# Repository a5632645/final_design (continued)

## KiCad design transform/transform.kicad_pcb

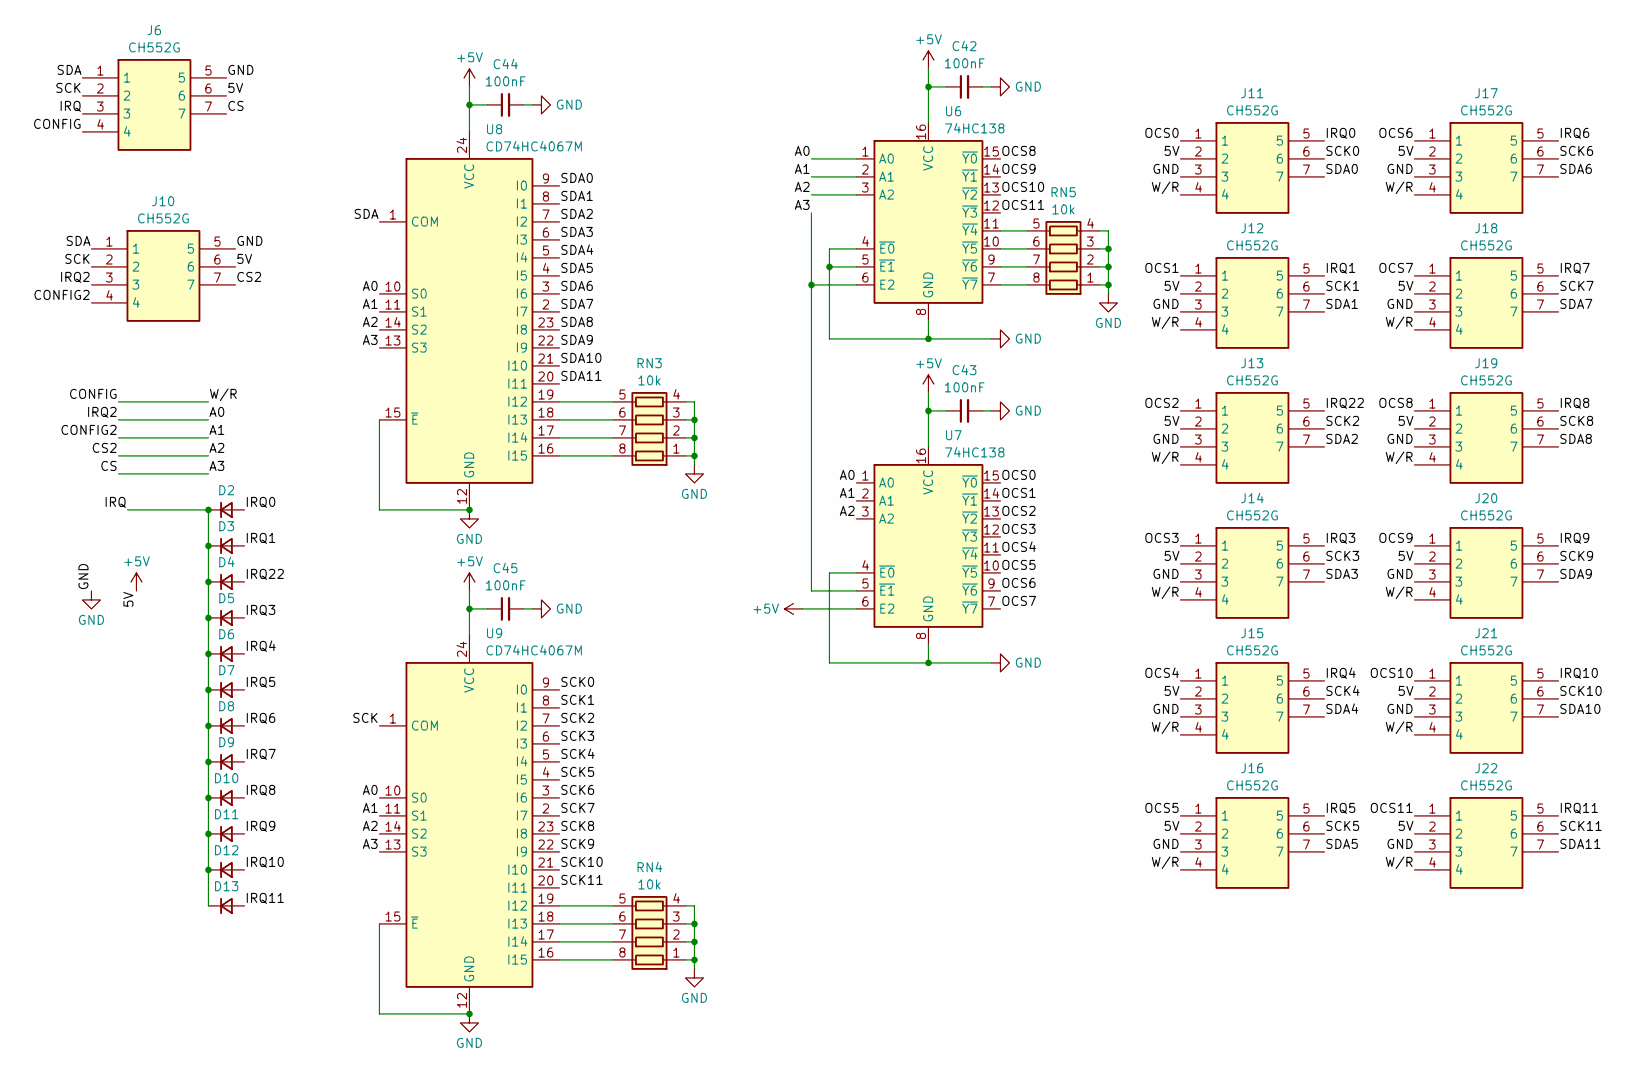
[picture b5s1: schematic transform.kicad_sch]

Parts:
C42, C43, C44, C45: 100nF; C_0603_1608Metric
D2, D3, D4, D5, D6, D7, D8, D9, D10, D11, D12, D13: D_Small; D_1206_3216Metric
J6, J10, J11, J12, J13, J14, J15, J16, J17, J18, J19, J20, J21, J22: CH552G; SM07B-SRSS-TB; Manufacturer_Part_Number SM07B-SRSS-TB (LF)(SN)
RN3, RN4, RN5: 10k; R_Array_Convex_4x0603
U6, U7: 74HC138; SOIC-16_3.9x9.9mm_P1.27mm
U8, U9: CD74HC4067M; SOIC-24W_7.5x15.4mm_P1.27mm

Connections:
+5V: C42.1, C43.1, C44.1, C45.1, J6.6, J10.6, J11.2, J12.2, J13.2, J14.2, J15.2, J16.2, J17.2, J18.2, J19.2, J20.2, J21.2, J22.2, U6.16 (VCC), U7.6 (E2), U7.16 (VCC), U8.24 (VCC), U9.24 (VCC)
/A0: J10.3, U6.1 (A0), U7.1 (A0), U8.10 (S0), U9.10 (S0)
/A1: J10.4, U6.2 (A1), U7.2 (A1), U8.11 (S1), U9.11 (S1)
/A2: J10.7, U6.3 (A2), U7.3 (A2), U8.14 (S2), U9.14 (S2)
/A3: J6.7, U6.6 (E2), U7.5 (~E1), U8.13 (S3), U9.13 (S3)
/CONFIG: J6.4, J11.4, J12.4, J13.4, J14.4, J15.4, J16.4, J17.4, J18.4, J19.4, J20.4, J21.4, J22.4
/IRQ: D2.1 (K), D3.1 (K), D4.1 (K), D5.1 (K), D6.1 (K), D7.1 (K), D8.1 (K), D9.1 (K), D10.1 (K), D11.1 (K), D12.1 (K), D13.1 (K), J6.3
/IRQ0: D2.2 (A), J11.5
/IRQ1: D3.2 (A), J12.5
/IRQ3: D5.2 (A), J14.5
/IRQ4: D6.2 (A), J15.5
/IRQ5: D7.2 (A), J16.5
/IRQ6: D8.2 (A), J17.5
/IRQ7: D9.2 (A), J18.5
/IRQ8: D10.2 (A), J19.5
/IRQ9: D11.2 (A), J20.5
/IRQ10: D12.2 (A), J21.5
/IRQ11: D13.2 (A), J22.5
/IRQ22: D4.2 (A), J13.5
/OCS0: J11.1, U7.15 (~Y0)
/OCS1: J12.1, U7.14 (~Y1)
/OCS2: J13.1, U7.13 (~Y2)
/OCS3: J14.1, U7.12 (~Y3)
/OCS4: J15.1, U7.11 (~Y4)
/OCS5: J16.1, U7.10 (~Y5)
/OCS6: J17.1, U7.9 (~Y6)
/OCS7: J18.1, U7.7 (~Y7)
/OCS8: J19.1, U6.15 (~Y0)
/OCS9: J20.1, U6.14 (~Y1)
/OCS10: J21.1, U6.13 (~Y2)
/OCS11: J22.1, U6.12 (~Y3)
/SCK: J6.2, J10.2, U9.1 (COM)
/SCK0: J11.6, U9.9 (I0)
/SCK1: J12.6, U9.8 (I1)
/SCK2: J13.6, U9.7 (I2)
/SCK3: J14.6, U9.6 (I3)
/SCK4: J15.6, U9.5 (I4)
/SCK5: J16.6, U9.4 (I5)
/SCK6: J17.6, U9.3 (I6)
/SCK7: J18.6, U9.2 (I7)
/SCK8: J19.6, U9.23 (I8)
/SCK9: J20.6, U9.22 (I9)
/SCK10: J21.6, U9.21 (I10)
/SCK11: J22.6, U9.20 (I11)
/SDA: J6.1, J10.1, U8.1 (COM)
/SDA0: J11.7, U8.9 (I0)
/SDA1: J12.7, U8.8 (I1)
/SDA2: J13.7, U8.7 (I2)
/SDA3: J14.7, U8.6 (I3)
/SDA4: J15.7, U8.5 (I4)
/SDA5: J16.7, U8.4 (I5)
/SDA6: J17.7, U8.3 (I6)
/SDA7: J18.7, U8.2 (I7)
/SDA8: J19.7, U8.23 (I8)
/SDA9: J20.7, U8.22 (I9)
/SDA10: J21.7, U8.21 (I10)
/SDA11: J22.7, U8.20 (I11)
GND: C42.2, C43.2, C44.2, C45.2, J6.5, J10.5, J11.3, J12.3, J13.3, J14.3, J15.3, J16.3, J17.3, J18.3, J19.3, J20.3, J21.3, J22.3, RN3.1 (R1.1), RN3.2 (R2.1), RN3.3 (R3.1), RN3.4 (R4.1), RN4.1 (R1.1), RN4.2 (R2.1), RN4.3 (R3.1), RN4.4 (R4.1), RN5.1 (R1.1), RN5.2 (R2.1), RN5.3 (R3.1), RN5.4 (R4.1), U6.4 (~E0), U6.5 (~E1), U6.8 (GND), U7.4 (~E0), U7.8 (GND), U8.12 (GND), U8.15 (~E), U9.12 (GND), U9.15 (~E)
unnamed: RN3.8 (R1.2), U8.16 (I15)
unnamed: RN3.7 (R2.2), U8.17 (I14)
unnamed: RN3.6 (R3.2), U8.18 (I13)
unnamed: RN3.5 (R4.2), U8.19 (I12)
unnamed: RN4.8 (R1.2), U9.16 (I15)
unnamed: RN4.7 (R2.2), U9.17 (I14)
unnamed: RN4.6 (R3.2), U9.18 (I13)
unnamed: RN4.5 (R4.2), U9.19 (I12)
unnamed: RN5.8 (R1.2), U6.7 (~Y7)
unnamed: RN5.7 (R2.2), U6.9 (~Y6)
unnamed: RN5.6 (R3.2), U6.10 (~Y5)
unnamed: RN5.5 (R4.2), U6.11 (~Y4)

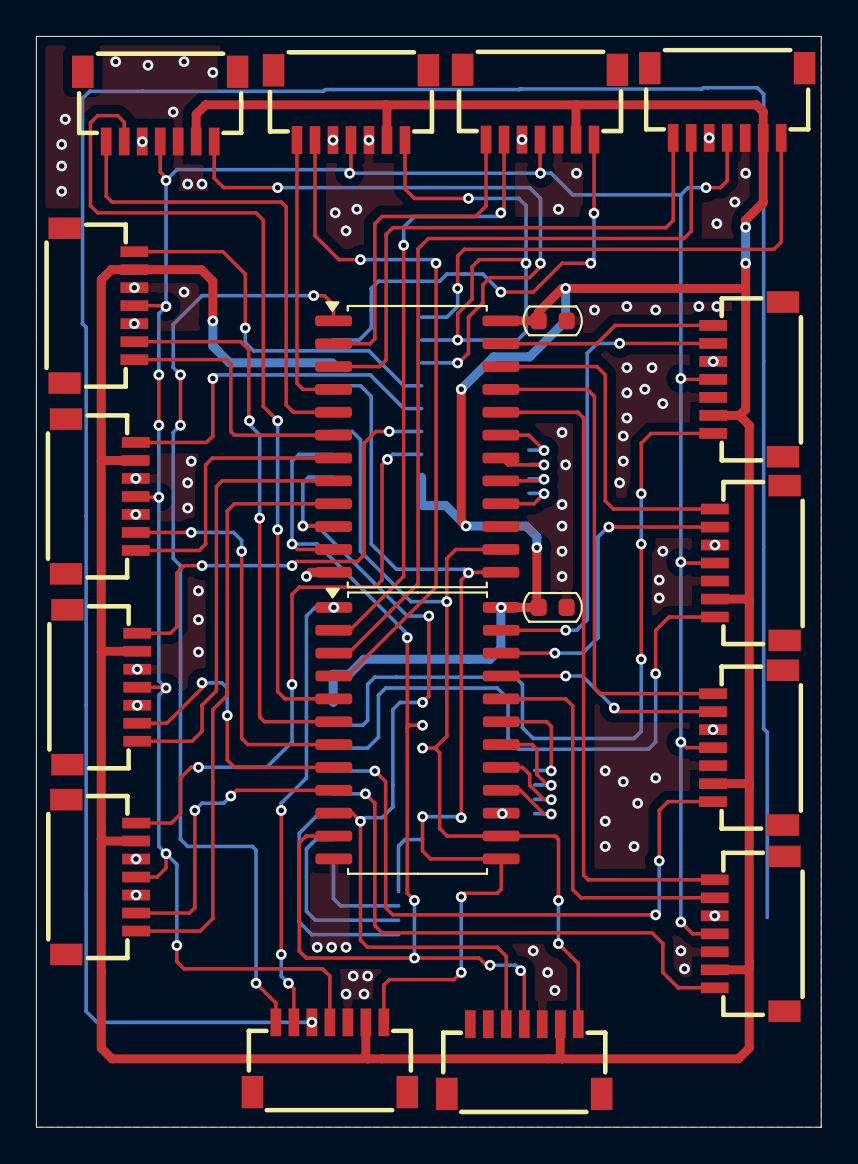
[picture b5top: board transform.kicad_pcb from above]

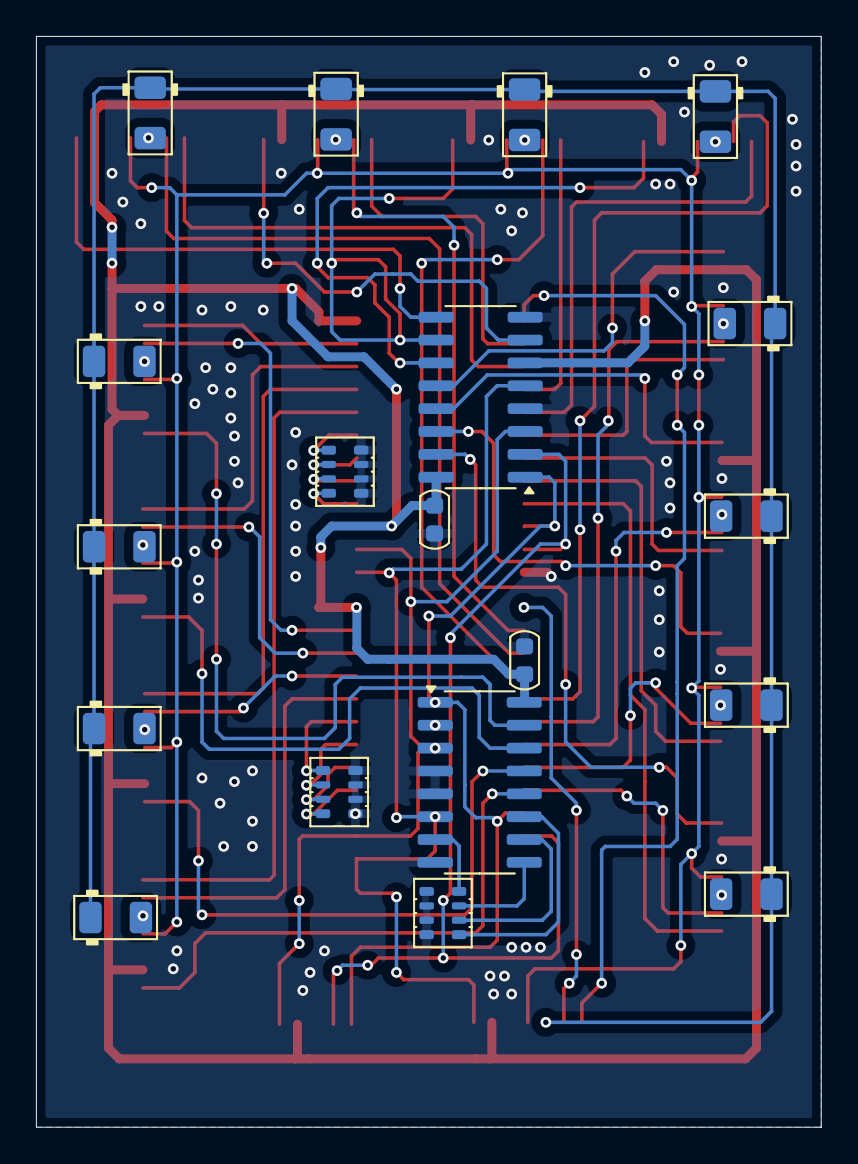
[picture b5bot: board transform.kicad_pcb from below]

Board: 2 copper layers, 43.6 x 60.6 mm, 37 parts (19 on the bottom side), 70 nets.

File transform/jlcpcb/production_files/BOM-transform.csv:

Comment,Designator,Footprint,LCSC,Quantity
10k,RN4,R_Array_Convex_4x0603,,1
CH552G,J17,SM07B-SRSS-TB,,1
CH552G,J11,SM07B-SRSS-TB,,1
CH552G,J14,SM07B-SRSS-TB,,1
CH552G,J22,SM07B-SRSS-TB,,1
CH552G,J12,SM07B-SRSS-TB,,1
CH552G,J13,SM07B-SRSS-TB,,1
CH552G,J15,SM07B-SRSS-TB,,1
CH552G,J16,SM07B-SRSS-TB,,1
CD74HC4067M,U8,SOIC-24W_7.5x15.4mm_P1.27mm,,1
74HC138,U6,SOIC-16_3.9x9.9mm_P1.27mm,,1
74HC138,U7,SOIC-16_3.9x9.9mm_P1.27mm,,1
CH552G,J21,SM07B-SRSS-TB,,1
CH552G,J20,SM07B-SRSS-TB,,1
CH552G,J19,SM07B-SRSS-TB,,1
CH552G,J18,SM07B-SRSS-TB,,1
CH552G,J10,SM07B-SRSS-TB,,1
CH552G,J6,SM07B-SRSS-TB,,1
CD74HC4067M,U9,SOIC-24W_7.5x15.4mm_P1.27mm,,1
10k,RN5,R_Array_Convex_4x0603,,1
10k,RN3,R_Array_Convex_4x0603,,1
D_Small,D13,D_1206_3216Metric,,1
D_Small,D12,D_1206_3216Metric,,1
D_Small,D11,D_1206_3216Metric,,1
D_Small,D10,D_1206_3216Metric,,1
D_Small,D9,D_1206_3216Metric,,1
D_Small,D8,D_1206_3216Metric,,1
D_Small,D7,D_1206_3216Metric,,1
D_Small,D6,D_1206_3216Metric,,1
D_Small,D5,D_1206_3216Metric,,1
D_Small,D4,D_1206_3216Metric,,1
D_Small,D3,D_1206_3216Metric,,1
D_Small,D2,D_1206_3216Metric,,1
100nF,C45,C_0603_1608Metric,,1
100nF,C44,C_0603_1608Metric,,1
100nF,C43,C_0603_1608Metric,,1
100nF,C42,C_0603_1608Metric,,1

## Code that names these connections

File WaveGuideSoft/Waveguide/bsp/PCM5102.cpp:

#include "PCM5102.hpp"

#include "stm32h7xx_hal.h"

#include "MemAttributes.hpp"
#include "SystemHook.hpp"

#include "FreeRTOS.h"
#include "task.h"
#include "semphr.h"

namespace bsp {

static I2S_HandleTypeDef hi2s_;
static DMA_HandleTypeDef hdma_;

MEM_DMA_SRAMD1 static StereoSample dmaBuffer_[CPCM5102::kBufferSize];
static volatile uint32_t offset_ = 0;
static SemaphoreHandle_t dmaSemHandle_ = NULL;
static StaticSemaphore_t dmaSem_;
constexpr auto kGenSize = CPCM5102::kBlockSize;

// --------------------------------------------------------------------------------
// public
// --------------------------------------------------------------------------------
void CPCM5102::Init() {
    // i2s init
    __HAL_RCC_SPI1_CLK_ENABLE();
    hi2s_.Instance = SPI1;
    hi2s_.Init.Mode = I2S_MODE_MASTER_TX;
    hi2s_.Init.Standard = I2S_STANDARD_PHILIPS;
    hi2s_.Init.DataFormat = I2S_DATAFORMAT_16B;
    hi2s_.Init.MCLKOutput = I2S_MCLKOUTPUT_ENABLE;
    hi2s_.Init.AudioFreq = kSampleRate;
    hi2s_.Init.CPOL = I2S_CPOL_LOW;
    hi2s_.Init.FirstBit = I2S_FIRSTBIT_MSB;
    hi2s_.Init.WSInversion = I2S_WS_INVERSION_DISABLE;
    hi2s_.Init.Data24BitAlignment = I2S_DATA_24BIT_ALIGNMENT_LEFT;
    hi2s_.Init.MasterKeepIOState = I2S_MASTER_KEEP_IO_STATE_DISABLE;
    HAL_I2S_Init(&hi2s_);

    // dma init
    __HAL_RCC_DMA1_CLK_ENABLE();
    hdma_.Instance = DMA1_Stream5;
    hdma_.Init.Request = DMA_REQUEST_SPI1_TX;
    hdma_.Init.Direction = DMA_MEMORY_TO_PERIPH;
    hdma_.Init.PeriphInc = DMA_PINC_DISABLE;
    hdma_.Init.MemInc = DMA_MINC_ENABLE;
    hdma_.Init.PeriphDataAlignment = DMA_PDATAALIGN_HALFWORD;
    hdma_.Init.MemDataAlignment = DMA_MDATAALIGN_HALFWORD;
    hdma_.Init.Mode = DMA_CIRCULAR;
    hdma_.Init.Priority = DMA_PRIORITY_VERY_HIGH;
    hdma_.Init.FIFOMode = DMA_FIFOMODE_DISABLE;
    HAL_DMA_Init(&hdma_);

    hi2s_.hdmatx = &hdma_;
    hdma_.Parent = &hi2s_;

    HAL_NVIC_EnableIRQ(DMA1_Stream5_IRQn);
    HAL_NVIC_SetPriority(DMA1_Stream5_IRQn, 6, 0);

    // i2s gpio init
    // PC4 -> MCLK
    // PA5 -> BCK
    // PA4-> WS
    // PA7 -> SDO
    __HAL_RCC_GPIOC_CLK_ENABLE();
    GPIO_InitTypeDef gpioCInit{};
    gpioCInit.Alternate = GPIO_AF5_SPI1;
    gpioCInit.Mode = GPIO_MODE_AF_PP;
    gpioCInit.Pin = GPIO_PIN_4;
    gpioCInit.Pull = GPIO_NOPULL;
    gpioCInit.Speed = GPIO_SPEED_FREQ_HIGH;
    HAL_GPIO_Init(GPIOC, &gpioCInit);

    __HAL_RCC_GPIOA_CLK_ENABLE();
    GPIO_InitTypeDef gpioAInit{};
    gpioAInit.Alternate = GPIO_AF5_SPI1;
    gpioAInit.Mode = GPIO_MODE_AF_PP;
    gpioAInit.Pin = GPIO_PIN_5 | GPIO_PIN_4 | GPIO_PIN_7;
    gpioAInit.Pull = GPIO_NOPULL;
    gpioAInit.Speed = GPIO_SPEED_FREQ_HIGH;
    HAL_GPIO_Init(GPIOA, &gpioAInit);

    // os param init
    dmaSemHandle_ = xSemaphoreCreateBinaryStatic(&dmaSem_);
    std::fill_n(dmaBuffer_, kBufferSize, StereoSample{});
}

void CPCM5102::Start() {
    HAL_I2S_Transmit_DMA(&hi2s_, (uint16_t*)dmaBuffer_, kBufferSize * 2);
}

void CPCM5102::Stop() {
    HAL_I2S_DMAStop(&hi2s_);
}

void CPCM5102::DeInit() {
    HAL_I2S_DeInit(&hi2s_);
    HAL_DMA_DeInit(&hdma_);
    dmaSemHandle_ = NULL;
}

std::span<StereoSample> CPCM5102::GetNextBlock() {
    xSemaphoreTake(dmaSemHandle_, portMAX_DELAY);
    return std::span<StereoSample>(dmaBuffer_ + offset_, kGenSize);
}

// --------------------------------------------------------------------------------
// ISR
// --------------------------------------------------------------------------------
extern "C" void DMA1_Stream5_IRQHandler() {
    HAL_DMA_IRQHandler(&hdma_);
}

extern "C" void HAL_I2S_TxHalfCpltCallback(I2S_HandleTypeDef*) {
    offset_ = 0;
    xSemaphoreGiveFromISR(dmaSemHandle_, nullptr);
}

extern "C" void HAL_I2S_TxCpltCallback(I2S_HandleTypeDef*) {
    offset_ = kGenSize;
    xSemaphoreGiveFromISR(dmaSemHandle_, nullptr);
}

extern "C" void HAL_I2S_ErrorCallback(I2S_HandleTypeDef* hi2s) {
    DEVICE_ERROR_CODE("AudioOut", "HAL_I2S_ErrorCallback", hi2s->ErrorCode);
}

}

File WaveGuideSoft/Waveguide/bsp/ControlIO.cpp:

#include "ControlIO.hpp"

#include <array>

#include "stm32h7xx_hal.h"
#include "stm32h7xx_ll_exti.h"
#include "stm32h7xx_ll_gpio.h"

#include "FreeRTOS.h"
#include "timers.h"
#include "semphr.h"

#include "SystemHook.hpp"
#include "MemAttributes.hpp"
#include "bsp/DebugIO.hpp"

// enacoder 1
#define ECA1_GPIO GPIOA
#define ECA1_PIN GPIO_PIN_3
#define ECA2_GPIO GPIOA
#define ECA2_PIN GPIO_PIN_2
#define ECA_IRQn EXTI3_IRQn
// enacoder 2
#define ECB1_GPIO GPIOA
#define ECB1_PIN GPIO_PIN_1
#define ECB2_GPIO GPIOA
#define ECB2_PIN GPIO_PIN_0
#define ECB_IRQn EXTI1_IRQn

namespace bsp {

static int32_t encoderValues_[CControlIO::kNumEncoders]{};
static uint32_t prevButtonState_{ 0xffffffff };
static uint32_t currButtonState_{ 0xffffffff };
static uint32_t tick_{};
static CControlIO::BtnCallback btnCallbacks_[CControlIO::kNumButtons]{};
static CControlIO::EncoderCallback encoderCallbacks_[CControlIO::kNumEncoders]{};

inline static void NullBtnCallback(ButtonEventArgs) {};
inline static void NullEncoderCallback(int32_t) {};

void CControlIO::Init() {
    /* 按键初始化 */
    __HAL_RCC_GPIOE_CLK_ENABLE();
    GPIO_InitTypeDef init{};
    init.Mode = GPIO_MODE_INPUT;
    init.Pin = GPIO_PIN_5 | GPIO_PIN_6 | GPIO_PIN_7 | GPIO_PIN_8 | GPIO_PIN_9 | GPIO_PIN_10 | GPIO_PIN_11 | GPIO_PIN_12 | GPIO_PIN_13 | GPIO_PIN_14;
    init.Pull = GPIO_PULLUP;
    init.Speed = GPIO_SPEED_FREQ_HIGH;
    HAL_GPIO_Init(GPIOE, &init);

    /* 编码器初始化 */
    __HAL_RCC_GPIOA_CLK_ENABLE();
    GPIO_InitTypeDef gpioInit{};
    gpioInit.Alternate = 0;
    gpioInit.Mode = GPIO_MODE_INPUT;
    gpioInit.Pin = ECA2_PIN;
    gpioInit.Pull = GPIO_NOPULL;
    gpioInit.Speed = GPIO_SPEED_FREQ_LOW;
    HAL_GPIO_Init(ECA2_GPIO, &gpioInit);
    gpioInit.Pin = ECB2_PIN;
    HAL_GPIO_Init(ECB2_GPIO, &gpioInit);
    gpioInit.Mode = GPIO_MODE_IT_RISING_FALLING;
    gpioInit.Pin = ECA1_PIN;
    HAL_GPIO_Init(ECA1_GPIO, &gpioInit);
    gpioInit.Pin = ECB1_PIN;
    HAL_GPIO_Init(ECB1_GPIO, &gpioInit);
    HAL_NVIC_SetPriority(ECA_IRQn, 10, 0);
    HAL_NVIC_EnableIRQ(ECA_IRQn);
    HAL_NVIC_SetPriority(ECB_IRQn, 10, 0);
    HAL_NVIC_EnableIRQ(ECB_IRQn);

    // reset callbacks
    std::fill_n(btnCallbacks_, kNumButtons, NullBtnCallback);
    std::fill_n(encoderCallbacks_, kNumEncoders, NullEncoderCallback);
}

void CControlIO::WaitForNextEvent() {
    xTaskDelayUntil(&tick_, pdMS_TO_TICKS(kScanMs));
    prevButtonState_ = currButtonState_;
    currButtonState_ = LL_GPIO_ReadInputPort(GPIOE);
}

void CControlIO::ProcessButtonEvents() {
    uint32_t mask = 1 << 14;
    for (uint32_t i = 0; i < kNumButtons; ++i) {
        auto changed = currButtonState_ ^ prevButtonState_;
        auto pressed = currButtonState_ & mask;
        auto state = ButtonState::kAttack;
        if (changed & mask) {
            if (pressed) {
                state = ButtonState::kAttack;
            }
            else {
                state = ButtonState::kRelease;
            }
        }
        else {
            if (pressed) {
                state = ButtonState::kHold;
            }
            else {
                state = ButtonState::kInit;
            }
        }
        if (state != ButtonState::kInit) {
            btnCallbacks_[i](state);
        }
        mask >>= 1;
    }
}

void CControlIO::ProcessEncoderEvents() {
    for (uint32_t i = 0; i < kNumEncoders; ++i) {
        if (encoderValues_[i] != 0) {
            encoderCallbacks_[i](encoderValues_[i]);
            encoderValues_[i] = 0;
        }
    }
}

void CControlIO::SetButtonCallback(ButtonId id, BtnCallback callback) {
    btnCallbacks_[static_cast<uint32_t>(id)] = callback;
}

void CControlIO::SetEncoderCallback(EncoderId id, EncoderCallback callback) {
    encoderCallbacks_[static_cast<uint32_t>(id)] = callback;
}

void CControlIO::UnsetButtonCallback(ButtonId id) {
    btnCallbacks_[static_cast<uint32_t>(id)] = NullBtnCallback;
}

void CControlIO::UnsetEncoderCallback(EncoderId id) {
    encoderCallbacks_[static_cast<uint32_t>(id)] = NullEncoderCallback;
}

void CControlIO::ResetButtonCallbacks() {
    std::fill_n(btnCallbacks_, kNumButtons, NullBtnCallback);
}

void CControlIO::ResetEncoderCallbacks() {
    std::fill_n(encoderCallbacks_, kNumEncoders, NullEncoderCallback);
}

static struct {
    bool flag1 : 1;
    bool init_nu1 : 1;
    bool flag2 : 1;
    bool init_nu2 : 1;
    bool flag3 : 1;
    bool init_nu3 : 1;
    bool flag4 : 1;
    bool init_nu4 : 1;
} encoderIrqFlags{};

void AddEncoderValue(EncoderId id, int32_t value) {
    auto idx = static_cast<uint32_t>(id);
    encoderValues_[idx] += value;
}

extern "C" void EXTI3_IRQHandler(void) {
    LL_EXTI_ClearFlag_0_31(LL_EXTI_LINE_3);
    auto keya = LL_GPIO_ReadInputPort(ECA1_GPIO) & ECA1_PIN;
    auto keyb = LL_GPIO_ReadInputPort(ECA2_GPIO) & ECA2_PIN;
    if (!encoderIrqFlags.init_nu1 && !keya) {
        encoderIrqFlags.flag1 = false;
        if (keyb) {
            encoderIrqFlags.flag1 = true;
        }
        encoderIrqFlags.init_nu1 = true;
    }

    if (encoderIrqFlags.init_nu1 && keya) {
        if (!keyb && encoderIrqFlags.flag1) {
            AddEncoderValue(EncoderId::kParam, -1);
        }
        if (keyb && !encoderIrqFlags.flag1) {
            AddEncoderValue(EncoderId::kParam, 1);
        }
        encoderIrqFlags.init_nu1 = false;
    }
}

extern "C" void EXTI1_IRQHandler(void) {
    LL_EXTI_ClearFlag_0_31(LL_EXTI_LINE_1);
    auto keya = LL_GPIO_ReadInputPort(ECB1_GPIO) & ECB1_PIN;
    auto keyb = LL_GPIO_ReadInputPort(ECB2_GPIO) & ECB2_PIN;

    if (!encoderIrqFlags.init_nu2 && !keya) {
        encoderIrqFlags.flag2 = false;
        if (keyb) {
            encoderIrqFlags.flag2 = true;
        }
        encoderIrqFlags.init_nu2 = true;
    }

    if (encoderIrqFlags.init_nu2 && keya) {
        if (!keyb && encoderIrqFlags.flag2) {
            AddEncoderValue(EncoderId::kValue, -1);
        }
        if (keyb && !encoderIrqFlags.flag2) {
            AddEncoderValue(EncoderId::kValue, 1);
        }
        encoderIrqFlags.init_nu2 = false;
    }
}

}

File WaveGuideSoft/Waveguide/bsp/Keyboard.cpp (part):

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#define IRQ_IRQn EXTI0_IRQn
#define IRQ2_GPIO GPIOB
#define IRQ2_PIN GPIO_PIN_2
#define CONFIG_GPIO GPIOB
#define CONFIG_PIN GPIO_PIN_10
#define CONFIG2_GPIO GPIOE
#define CONFIG2_PIN GPIO_PIN_15

#define WRITE_READ_GPIO CONFIG_GPIO
#define WRITE_READ_PIN CONFIG_PIN
#define A0_GPIO IRQ2_GPIO
#define A0_PIN IRQ2_PIN
#define A1_GPIO CONFIG2_GPIO
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    HAL_NVIC_SetPriority(SPI6_IRQn, 10, 0);

    // spi gpio init
    // PB4 -> MISO
    // PB3 -> SCK
    // PD3 -> CS
    // PD1 -> IRQ
    __HAL_RCC_GPIOB_CLK_ENABLE();
    GPIO_InitTypeDef gpioInit{};
    gpioInit.Mode = GPIO_MODE_AF_PP;
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    gpioInit.Alternate = GPIO_AF8_SPI6;
    HAL_GPIO_Init(GPIOB, &gpioInit);

    // pins config
    __HAL_RCC_GPIOC_CLK_ENABLE();
    __HAL_RCC_GPIOB_CLK_ENABLE();
    __HAL_RCC_GPIOE_CLK_ENABLE();
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
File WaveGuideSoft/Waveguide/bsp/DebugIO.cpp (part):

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        HAL_UART_Init(&huart_);
    }
    {
        // // TX -> PA2
        // // RX -> PA3
        // __HAL_RCC_GPIOA_CLK_ENABLE();
        // GPIO_InitTypeDef init{
        //     .Pin = GPIO_PIN_2,
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        // };
        // HAL_GPIO_Init(GPIOA, &init);

        // TX -> PA9
        // RX -> PA10
        __HAL_RCC_GPIOA_CLK_ENABLE();
        GPIO_InitTypeDef init{
            .Pin = GPIO_PIN_9,
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
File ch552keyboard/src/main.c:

#include "system.h"
#include "gpio.h"
#include "delay.h"
#include "uart.h"
#include "touchkey.h"
#include "pwm.h"

#include <stdint.h>
#include <stdio.h>
#include <string.h>
#include "ch554.h"
#include "ch554_usb.h"

// --------------------------------------------------------------------------------
// timer
// --------------------------------------------------------------------------------
static void Timer_Init(void);
static void Timer_Interrupt(void) __interrupt(INT_NO_TMR2);
static uint16_t Timer_GetTime(void);
static volatile uint16_t timerTick_ = 0;
#define SPI_TIMEOUT_MS 5

// --------------------------------------------------------------------------------
// Touchkey Slider
// --------------------------------------------------------------------------------
#define TIN0_PIN P11
#define TIN1_PIN P14
#define TIN2_PIN P15
#define TKEY_DOWN_THRESHOLD 2000
#define TKEY_UP_THRESHOLD 500
#define TKEY_POS_SCALE 0x7f
static const __code enum TouchKeyChannel tkeyChannelTable[] = {
    TK_P11, TK_P15, TK_P14
};
#define TKEY_NUM (sizeof(tkeyChannelTable) / sizeof(enum TouchKeyChannel))

static void TouchKey_Init(void);
static uint8_t currentTkey = 0;
static volatile int8_t tkeyFingerPosition = 0;
uint16_t touchkeyFreeValues[TKEY_NUM];
uint16_t absValues[TKEY_NUM];
uint8_t pressFlag = 0;

// --------------------------------------------------------------------------------
// OH49E HALL ADC
// --------------------------------------------------------------------------------
#define ADC_PIN P32
static void HallADC_Init(void);
static volatile uint8_t hallAdcValue = 0;
static uint8_t lowAdcThreadhold = 0;
static uint8_t highAdcThreadhold = 0;

// --------------------------------------------------------------------------------
// Key SPI Commuunication
// --------------------------------------------------------------------------------
#define SPI_SCK_PIN P17
#define SPI_MISO_PIN P16
#define SPI_CS_PIN P33
#define SPI_SLAVE_SCS_PIN P14
#define SPI_WR_PIN P31
#define SPI_IRQ_ENABLE_PIN P34 // 下降沿产生IRQ
// TODO: 焊接所有的MCS和CS_PREV

static void KeyCommunication_Init(void);
static void KeyCommunication_Send(void);
static void KeyCommunication_Receive(void);

inline uint16_t Abs(uint16_t a, uint16_t b) {
    if (a > b) {
        return a - b;
    }
    else {
        return 0;
    }
}

void main(void) {
    CLK_config();
    DLY_ms(5);

    HallADC_Init();
    TouchKey_Init();
    KeyCommunication_Init();
    Timer_Init();
    EA = 1;

    for (;;) {
        if (PIN_read(SPI_CS_PIN) == 0 && currentTkey != 2) {
            if (PIN_read(SPI_WR_PIN) == 0) {
                KeyCommunication_Send();
            }
            else {
                KeyCommunication_Receive();
            }
        }

        if (ADC_START == 0) {
            hallAdcValue = ADC_DATA;
            ADC_START = 1;
        }

        if (TouchKey_Ready() == 1) {
            uint16_t keyData = TKEY_DAT;

            // uint16_t diff = Abs(touchkeyFreeValues[currentTkey], keyData);
            uint16_t diff = 0;
            if (touchkeyFreeValues[currentTkey] > keyData) {
                diff = touchkeyFreeValues[currentTkey] - keyData;
            }
            uint8_t mask = 1 << currentTkey;
            if (diff < TKEY_UP_THRESHOLD) {
                if (pressFlag & mask) {
                    pressFlag &= ~mask;
                }
            }
            else if (diff > TKEY_DOWN_THRESHOLD) {
                if (!(pressFlag & mask)) {
                    pressFlag |= mask;
                }
            }

            absValues[currentTkey] = diff;
            ++currentTkey;
            if (currentTkey >= TKEY_NUM) {
                currentTkey = 0;

                if (pressFlag) {
                    int16_t denominator = (absValues[0] + absValues[1] + absValues[2]) / TKEY_POS_SCALE;
                    if (denominator != 0) {
                        int16_t nominator = absValues[2] - absValues[0];
                        int16_t div = nominator / denominator;
                        if (div < -TKEY_POS_SCALE) tkeyFingerPosition = -TKEY_POS_SCALE;
                        else if (div > TKEY_POS_SCALE) tkeyFingerPosition = TKEY_POS_SCALE;
                        else tkeyFingerPosition = div;
                    }
                }
                else {
                    tkeyFingerPosition = 0;
                }
            }

            TouchKey_Channel(tkeyChannelTable[currentTkey]);
        }
    }
}

#define TIMER2_FREQ (F_CPU / 12)
#define TIMER2_MS 1
#define TIMER2_RELOAD (0xffff - TIMER2_FREQ * TIMER2_MS / 1000 + 1)
void Timer_Init(void) {
    T2MOD &= ~(bTMR_CLK | bT2_CLK); // Fsys/12
    RCAP2 = TIMER2_RELOAD;
    T2COUNT = TIMER2_RELOAD;
    TR2 = 1;
    ET2 = 1;
    TF2 = 0; // !need manual clear
}

void Timer_Interrupt(void) __interrupt(INT_NO_TMR2) {
    TF2 = 0;
    ++timerTick_;
}

uint16_t Timer_GetTime(void) {
    return timerTick_;
}

// ---------------------------------------------------------------------------------
static void TouchKey_Init(void) {
    PIN_input(TIN0_PIN);
    PIN_input(TIN1_PIN);
    PIN_input(TIN2_PIN);
    TouchKey_Fast();
    for (uint8_t i = 0; i < TKEY_NUM; i++) {
        touchkeyFreeValues[i] = TouchKey_PollRead(tkeyChannelTable[i]);
    }
    
    TouchKey_Channel(tkeyChannelTable[0]);
}                

void HallADC_Init(void) {
    PIN_input(ADC_PIN);
    ADC_enable();
    ADC_fast();
    ADC_input(ADC_PIN);
    ADC_START = 1;
}

void KeyCommunication_Init(void) {
    PIN_input(SPI_CS_PIN);
    PIN_input(SPI_WR_PIN);
    PIN_output(SPI_IRQ_ENABLE_PIN);
    PIN_low(SPI_IRQ_ENABLE_PIN);
    IT1 = 1;
    IE1 = 0;
}

void KeyCommunication_Send(void) {
    // SPI设置
    PIN_high(SPI_IRQ_ENABLE_PIN);
    DLY_us(20);
    PIN_output(SPI_SLAVE_SCS_PIN);
    SCS = 1;
    SPI0_SETUP = bS0_MODE_SLV;
    SPI0_CTRL = bS0_2_WIRE | bS0_CLR_ALL | bS0_AUTO_IF | bS0_MISO_OE;
    SPI0_CTRL &= ~bS0_CLR_ALL;
    PIN_output(SPI_MISO_PIN);
    PIN_input(SPI_SCK_PIN);

    SPI0_S_PRE = 0b11011000;
    SCS = 0;
    PIN_low(SPI_IRQ_ENABLE_PIN);// 请求以及CH442E转发送
    while (S0_IF_BYTE == 0 && PIN_read(SPI_CS_PIN) == 0) {}
    S0_IF_BYTE  = 0;
    SPI0_DATA = 0b10101010;
    while (S0_IF_BYTE  == 0 && PIN_read(SPI_CS_PIN) == 0) {}
    S0_IF_BYTE  = 0;
    SPI0_DATA = hallAdcValue;
    while (S0_IF_BYTE  == 0 && PIN_read(SPI_CS_PIN) == 0) {}
    S0_IF_BYTE  = 0;
    SPI0_DATA = tkeyFingerPosition;
    while (S0_IF_BYTE  == 0 && PIN_read(SPI_CS_PIN) == 0) {}
    S0_IF_BYTE  = 0;

    PIN_input(SPI_SLAVE_SCS_PIN);
}

void KeyCommunication_Receive(void) {
    // SPI设置
    PIN_high(SPI_IRQ_ENABLE_PIN);
    DLY_us(20);
    PIN_output(SPI_SLAVE_SCS_PIN);
    SCS = 1;
    SPI0_SETUP = bS0_MODE_SLV;
    SPI0_CTRL = bS0_DATA_DIR | bS0_2_WIRE | bS0_AUTO_IF | bS0_CLR_ALL;
    SPI0_CTRL &= ~bS0_CLR_ALL;
    PIN_input(SPI_MISO_PIN);
    PIN_input(SPI_SCK_PIN);

    SCS = 0;
    PIN_low(SPI_IRQ_ENABLE_PIN);// 请求以及CH442E转发送
    while (S0_IF_BYTE == 0 && PIN_read(SPI_CS_PIN) == 0) {}
    S0_IF_BYTE  = 0;
    highAdcThreadhold = SPI0_DATA;
    while (S0_IF_BYTE  == 0 && PIN_read(SPI_CS_PIN) == 0) {}
    S0_IF_BYTE  = 0;
    lowAdcThreadhold = SPI0_DATA;
    SCS = 1;

    PIN_input(SPI_SLAVE_SCS_PIN);
}

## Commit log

2025-05-23 init
2025-05-23 something lost
2025-05-28 更新 README.md
